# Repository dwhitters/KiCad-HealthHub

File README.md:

# KiCad-HealthHub
Schematic and PCB layout for the health hub.

## Overview
This PCB provides basic signal processing for an ECG input. The processed signal is then fed into a bluetooth module that can be used to provide data to a corresponding phone app, such as https://github.com/DaveAldon/Health-Hub-Mobile. Additional microcontroller pins are broken out to facilitate development of additional features.

## Images
Front

Back

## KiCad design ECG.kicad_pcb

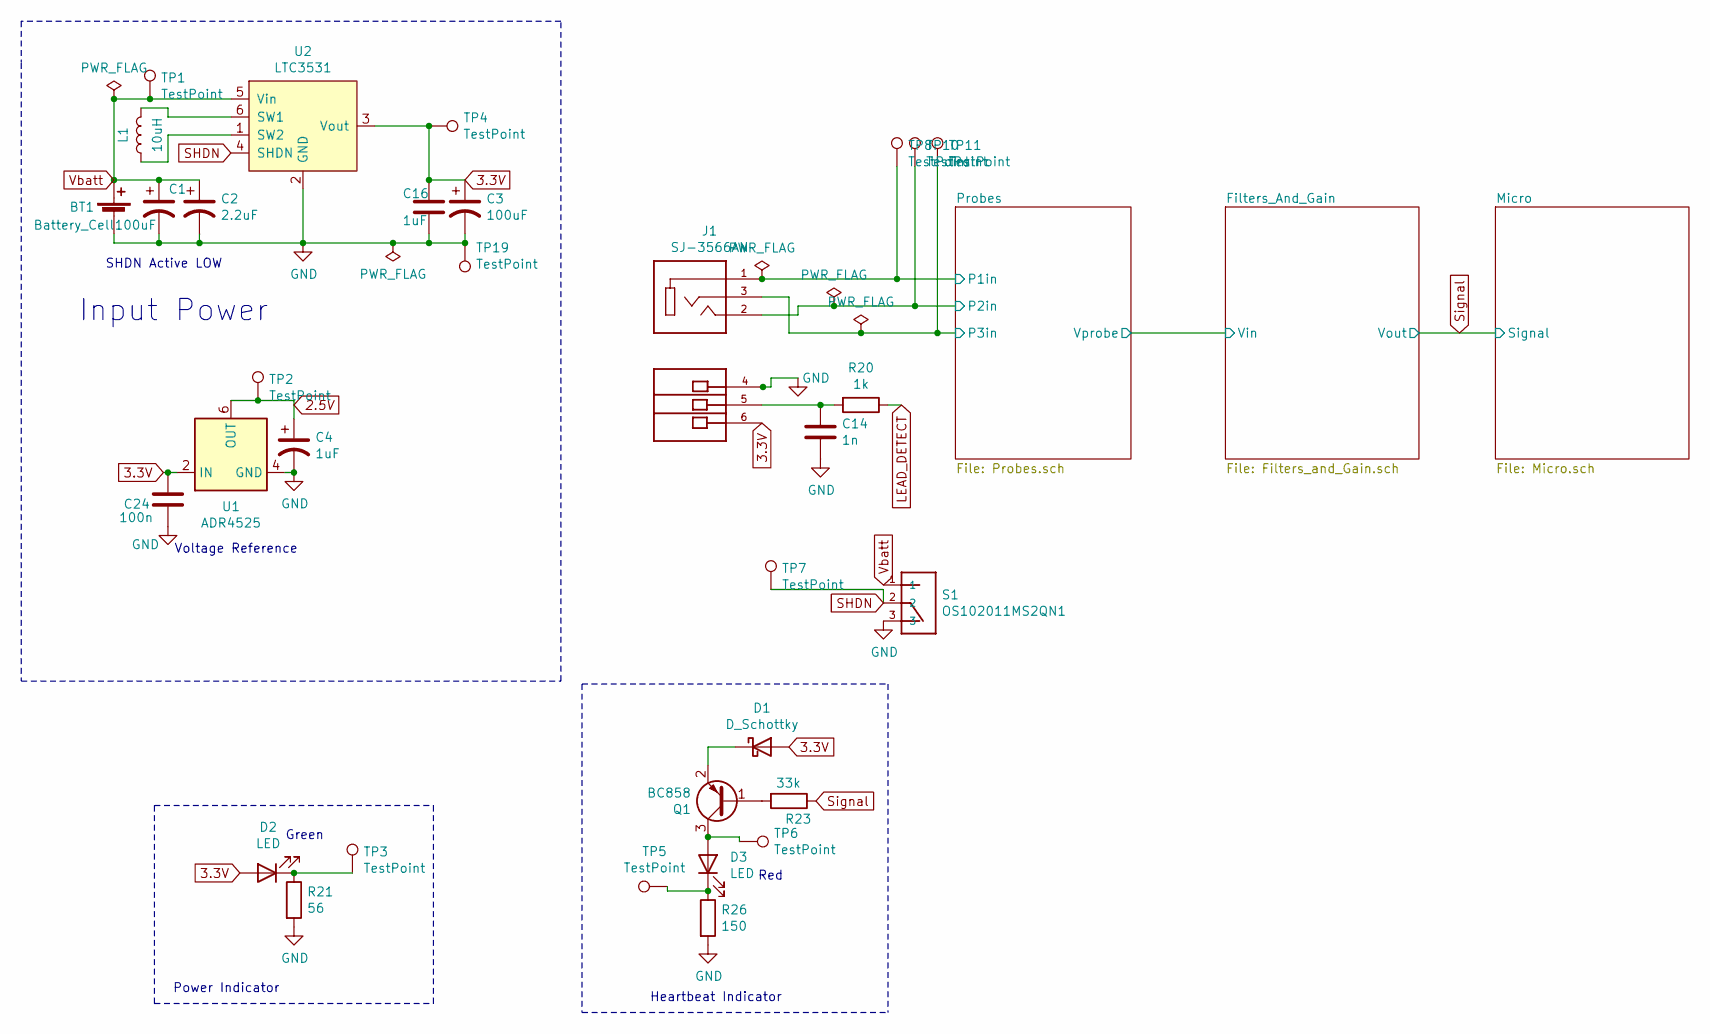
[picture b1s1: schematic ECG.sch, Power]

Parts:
BT1: Battery_Cell; BatteryHolder_Keystone_3008_1x2450
C1, C3: 100uF; CP_Elec_6.3x5.3
C2: 2.2uF; CP_Elec_4x5.7
C4: 1uF; C_0805_2012Metric_Pad1.18x1.45mm_HandSolder
C14: 1n; C_0805_2012Metric_Pad1.18x1.45mm_HandSolder
C16: 1uF; CP_Elec_4x5.3
C24: 100n; C_0805_2012Metric_Pad1.18x1.45mm_HandSolder
D1: D_Schottky; D_0603_1608Metric_Pad1.05x0.95mm_HandSolder
D2, D3: LED; D_0603_1608Metric_Pad1.05x0.95mm_HandSolder
J1: SJ-3566AN; CUI_SJ-3566AN
L1: 10uH; L_Sumida_CDRH5D28
Q1: BC858; SOT-23
R20: 1k; R_0805_2012Metric_Pad1.20x1.40mm_HandSolder
R21: 56; R_0805_2012Metric_Pad1.20x1.40mm_HandSolder
R23: 33k; R_0805_2012Metric_Pad1.20x1.40mm_HandSolder
R26: 150; R_0805_2012Metric_Pad1.20x1.40mm_HandSolder
S1: OS102011MS2QN1; SW_OS102011MS2QN1
TP1, TP3, TP5, TP6, TP7, TP8, TP10, TP11: TestPoint; TestPoint_Pad_D2.0mm
TP2, TP4, TP19: TestPoint; TestPoint_Pad_D4.0mm
U1: ADR4525; SOIC-8_3.9x4.9mm_P1.27mm
U2: LTC3531; TSOT-23-6

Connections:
2.5V: C4.1, TP2.1, U1.6 (OUT); also elsewhere on the board
3.3V: C3.1, C16.1, C24.1, D1.2 (A), D2.2 (A), J1.6, TP4.1, U1.2 (IN), U2.3 (Vout); also elsewhere on the board
/Probes/P1in: J1.1, TP8.1; also elsewhere on the board
/Probes/P2in: J1.2, TP10.1; also elsewhere on the board
/Probes/P3in: J1.3, TP11.1; also elsewhere on the board
GND: BT1.2 (-), C1.2, C2.2, C3.2, C4.2, C14.2, C16.2, C24.2, J1.4, R21.2, R26.2, S1.3, TP19.1, U1.4 (GND), U2.2 (GND); also elsewhere on the board
LEAD_DETECT: R20.1; also elsewhere on the board
unnamed: C14.1, J1.5, R20.2
unnamed: D1.1 (K), Q1.2 (E)
unnamed: D2.1 (K), R21.1, TP3.1
unnamed: D3.1 (K), R26.1, TP5.1
unnamed: D3.2 (A), Q1.3 (C), TP6.1
unnamed: L1.1, U2.1 (SW2)
unnamed: L1.2, U2.6 (SW1)
unnamed: Q1.1 (B), R23.2
SHDN: S1.2, TP7.1, U2.4 (SHDN); also elsewhere on the board
Signal: R23.1; also elsewhere on the board
Vbatt: BT1.1 (+), C1.1, C2.1, S1.1, TP1.1, U2.5 (Vin); also elsewhere on the board

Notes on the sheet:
Input Power
Voltage Reference
SHDN Active LOW
Power Indicator
Green
Red
Heartbeat Indicator

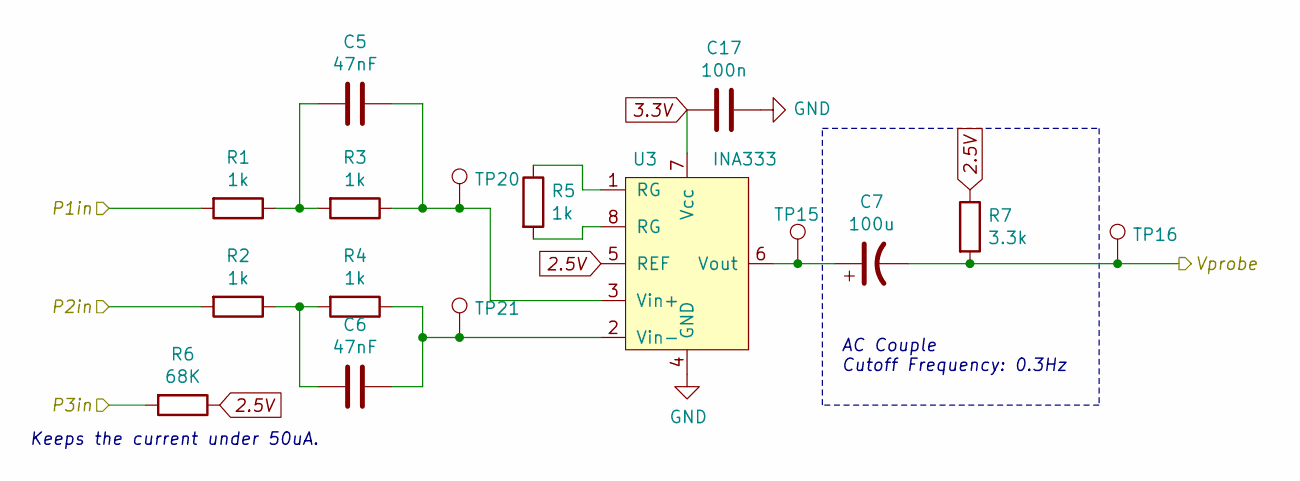
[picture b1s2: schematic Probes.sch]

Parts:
C5, C6: 47nF; C_0805_2012Metric_Pad1.18x1.45mm_HandSolder
C7: 100u; C_1210_3225Metric_Pad1.33x2.70mm_HandSolder
C17: 100n; C_0805_2012Metric_Pad1.18x1.45mm_HandSolder
R1, R2, R3, R4, R5: 1k; R_0805_2012Metric_Pad1.20x1.40mm_HandSolder
R6: 68K; R_0805_2012Metric_Pad1.20x1.40mm_HandSolder
R7: 3.3k; R_0805_2012Metric_Pad1.20x1.40mm_HandSolder
TP15, TP16, TP20, TP21: TestPoint; TestPoint_Pad_D2.0mm
U3: INA333; VSSOP-8_3.0x3.0mm_P0.65mm

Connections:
2.5V: R6.1, R7.1, U3.5 (REF); also elsewhere on the board
3.3V: C17.2, U3.7 (Vcc); also elsewhere on the board
/Filters_And_Gain/Vin: C7.2, R7.2, TP16.1; also elsewhere on the board
/Probes/P1in: R1.2; also elsewhere on the board
/Probes/P2in: R2.2; also elsewhere on the board
/Probes/P3in: R6.2; also elsewhere on the board
GND: C17.1, U3.4 (GND); also elsewhere on the board
unnamed: C5.1, R3.1, TP20.1, U3.3 (Vin+)
unnamed: C5.2, R1.1, R3.2
unnamed: C6.1, R4.1, TP21.1, U3.2 (Vin-)
unnamed: C6.2, R2.1, R4.2
unnamed: C7.1, TP15.1, U3.6 (Vout)
unnamed: R5.1, U3.1 (RG)
unnamed: R5.2, U3.8 (RG)

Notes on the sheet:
Keeps the current under 50uA.
AC Couple Cutoff Frequency: 0.3Hz

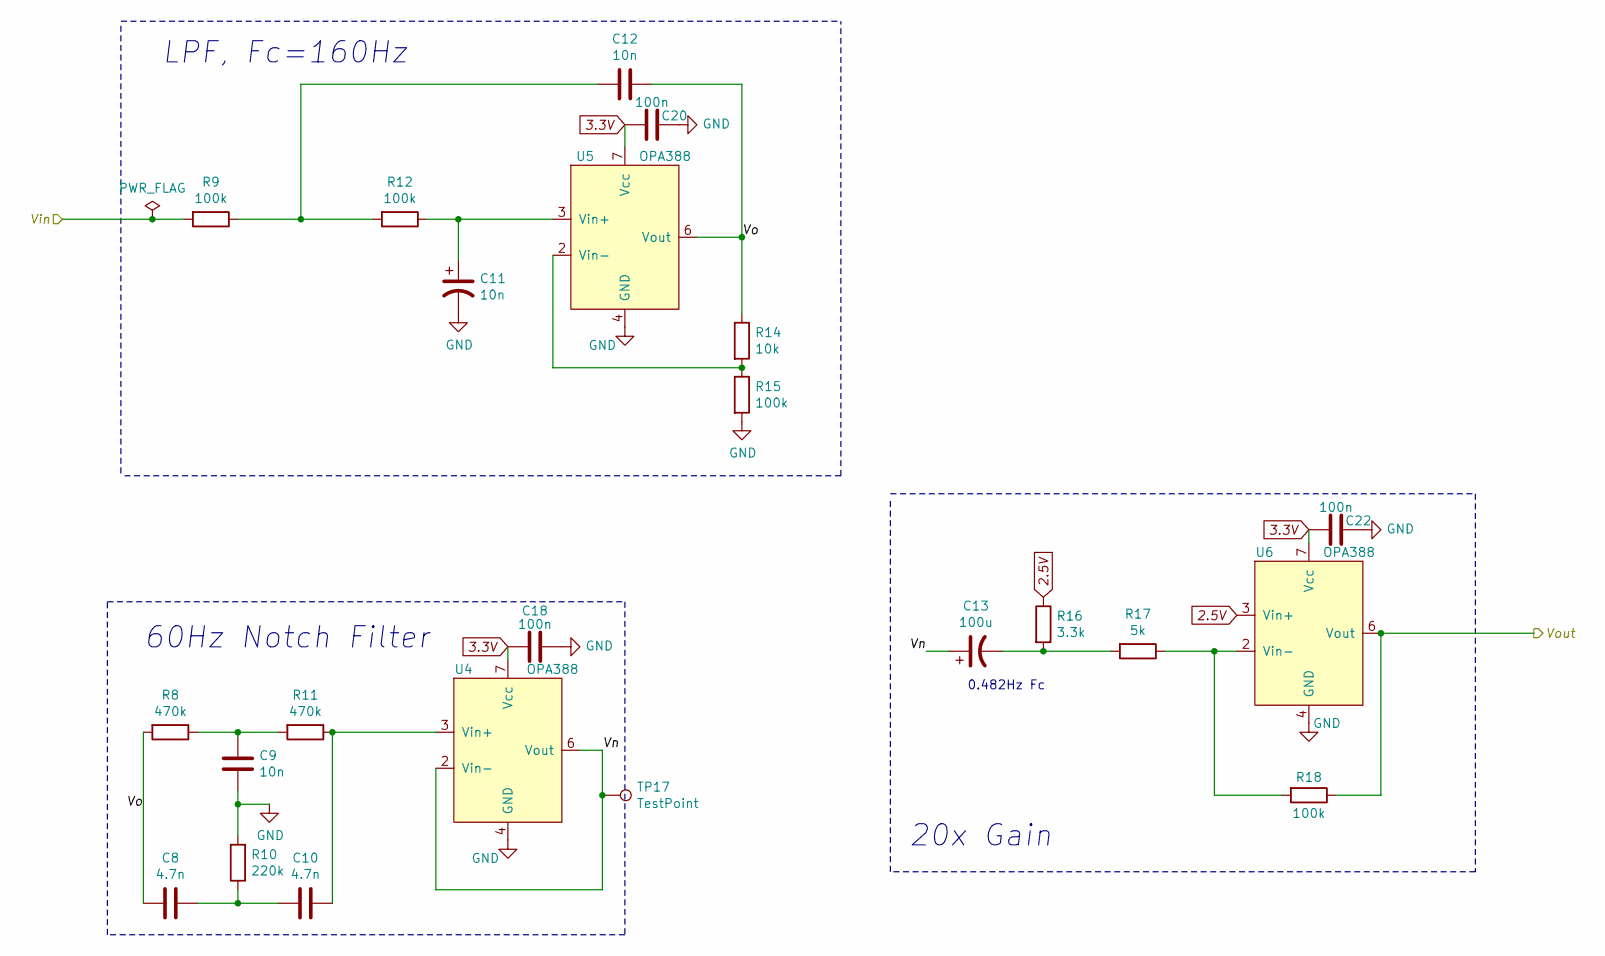
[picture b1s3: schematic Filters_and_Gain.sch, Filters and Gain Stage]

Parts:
C8, C10: 4.7n; C_0805_2012Metric_Pad1.18x1.45mm_HandSolder
C9, C11, C12: 10n; C_0805_2012Metric_Pad1.18x1.45mm_HandSolder
C13: 100u; C_1210_3225Metric_Pad1.33x2.70mm_HandSolder
C18, C20, C22: 100n; C_0805_2012Metric_Pad1.18x1.45mm_HandSolder
R8, R11: 470k; R_0805_2012Metric_Pad1.20x1.40mm_HandSolder
R9, R12, R15, R18: 100k; R_0805_2012Metric_Pad1.20x1.40mm_HandSolder
R10: 220k; R_0805_2012Metric_Pad1.20x1.40mm_HandSolder
R14: 10k; R_0805_2012Metric_Pad1.20x1.40mm_HandSolder
R16: 3.3k; R_0805_2012Metric_Pad1.20x1.40mm_HandSolder
R17: 5k; R_0805_2012Metric_Pad1.20x1.40mm_HandSolder
TP17: TestPoint; TestPoint_Pad_D2.0mm
U4, U5, U6: OPA388; SOIC-8_3.9x4.9mm_P1.27mm

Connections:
2.5V: R16.1, U6.3 (Vin+); also elsewhere on the board
3.3V: C18.1, C20.1, C22.1, U4.7 (Vcc), U5.7 (Vcc), U6.7 (Vcc); also elsewhere on the board
/Filters_And_Gain/Vin: R9.2; also elsewhere on the board
/Filters_And_Gain/Vn: C13.1, TP17.1, U4.2 (Vin-), U4.6 (Vout)
/Filters_And_Gain/Vo: C8.2, C12.2, R8.2, R14.1, U5.6 (Vout)
GND: C9.1, C11.2, C18.2, C20.2, C22.2, R10.2, R15.2, U4.4 (GND), U5.4 (GND), U6.4 (GND); also elsewhere on the board
unnamed: C9.2, R8.1, R11.2
unnamed: C10.1, R11.1, U4.3 (Vin+)
unnamed: C8.1, C10.2, R10.1
unnamed: C11.1, R12.1, U5.3 (Vin+)
unnamed: C12.1, R9.1, R12.2
unnamed: C13.2, R16.2, R17.2
unnamed: R14.2, R15.1, U5.2 (Vin-)
unnamed: R17.1, R18.2, U6.2 (Vin-)
Signal: R18.1, U6.6 (Vout); also elsewhere on the board

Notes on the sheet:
LPF, Fc=160Hz
20x Gain
0.482Hz Fc
60Hz Notch Filter

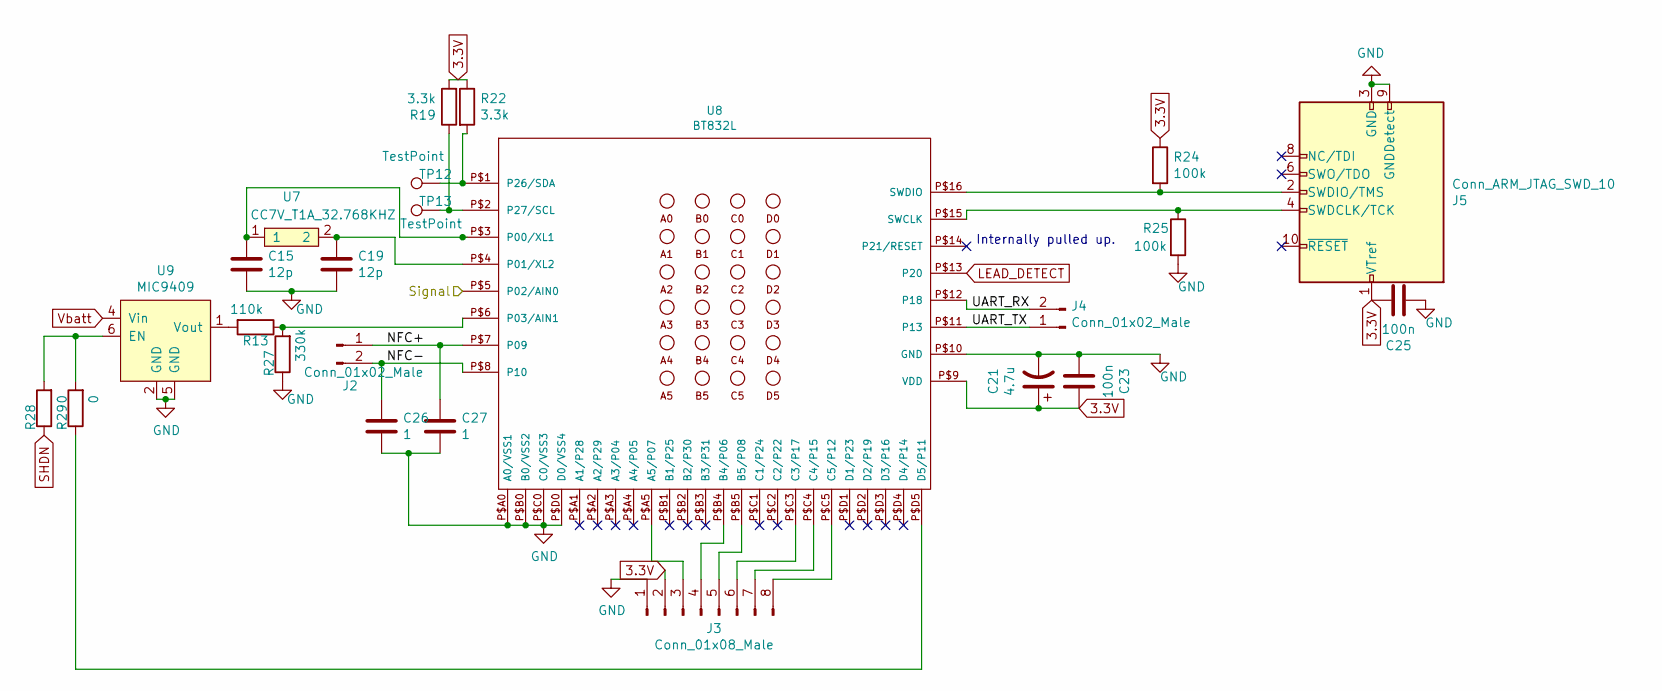
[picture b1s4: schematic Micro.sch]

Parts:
C15, C19: 12p; C_0805_2012Metric_Pad1.18x1.45mm_HandSolder
C21: 4.7u; CP_Elec_4x5.3
C23, C25: 100n; C_0805_2012Metric_Pad1.18x1.45mm_HandSolder
C26, C27: 1; C_0805_2012Metric_Pad1.18x1.45mm_HandSolder
J2, J4: Conn_01x02_Male; PinHeader_1x02_P2.00mm_Vertical
J3: Conn_01x08_Male; PinHeader_1x08_P2.00mm_Vertical
J5: Conn_ARM_JTAG_SWD_10; PinHeader_2x05_P1.27mm_Vertical_SMD
R13: 110k; R_0805_2012Metric_Pad1.20x1.40mm_HandSolder
R19, R22: 3.3k; R_0805_2012Metric_Pad1.20x1.40mm_HandSolder
R24, R25: 100k; R_0805_2012Metric_Pad1.20x1.40mm_HandSolder
R27: 330k; R_0805_2012Metric_Pad1.20x1.40mm_HandSolder
R28, R29: 0; R_0402_1005Metric_Pad0.72x0.64mm_HandSolder
TP12, TP13: TestPoint; TestPoint_Pad_D2.0mm
U7: CC7V_T1A_32.768KHZ; CC7V_T1A
U8: BT832L; BT832-BT832L
U9: MIC9409; SOT-363_SC-70-6_Handsoldering

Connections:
3.3V: C21.1, C23.1, C25.1, J3.2, J5.1 (VTref), R19.2, R22.1, R24.1, U8.P$9 (VDD); also elsewhere on the board
/Micro/NFC+: C27.1, J2.1, U8.P$7 (P09)
/Micro/NFC-: C26.1, J2.2, U8.P$8 (P10)
/Micro/UART_RX: J4.2, U8.P$12 (P18)
/Micro/UART_TX: J4.1, U8.P$11 (P13)
GND: C15.2, C19.2, C21.2, C23.2, C25.2, C26.2, C27.2, J3.1, J5.3 (GND), J5.5 (GND), J5.9 (GNDDetect), R25.2, R27.1, U8.P$10 (GND), U8.P$A0 (A0/VSS1), U8.P$B0 (B0/VSS2), U8.P$C0 (C0/VSS3), U8.P$D0 (D0/VSS4), U9.2 (GND), U9.5 (GND); also elsewhere on the board
LEAD_DETECT: U8.P$13 (P20); also elsewhere on the board
unnamed: C15.1, U7.1, U8.P$3 (P00/XL1)
unnamed: C19.1, U7.2, U8.P$4 (P01/XL2)
unnamed: J3.3, U8.P$A5 (A5/P07)
unnamed: J3.4, U8.P$B4 (B4/P06)
unnamed: J3.5, U8.P$B5 (B5/P08)
unnamed: J3.6, U8.P$C3 (C3/P17)
unnamed: J3.7, U8.P$C4 (C4/P15)
unnamed: J3.8, U8.P$C5 (C5/P12)
unnamed: J5.2 (SWDIO/TMS), R24.2, U8.P$16 (SWDIO)
unnamed: J5.4 (SWDCLK/TCK), R25.1, U8.P$15 (SWCLK)
unnamed: R13.1, R27.2, U8.P$6 (P03/AIN1)
unnamed: R13.2, U9.1 (Vout)
unnamed: R19.1, TP13.1, U8.P$2 (P27/SCL)
unnamed: R22.2, TP12.1, U8.P$1 (P26/SDA)
unnamed: R28.2, R29.2, U9.6 (EN)
unnamed: R29.1, U8.P$D5 (D5/P11)
SHDN: R28.1; also elsewhere on the board
Signal: U8.P$5 (P02/AIN0); also elsewhere on the board
Vbatt: U9.4 (Vin); also elsewhere on the board

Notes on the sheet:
Internally pulled up.

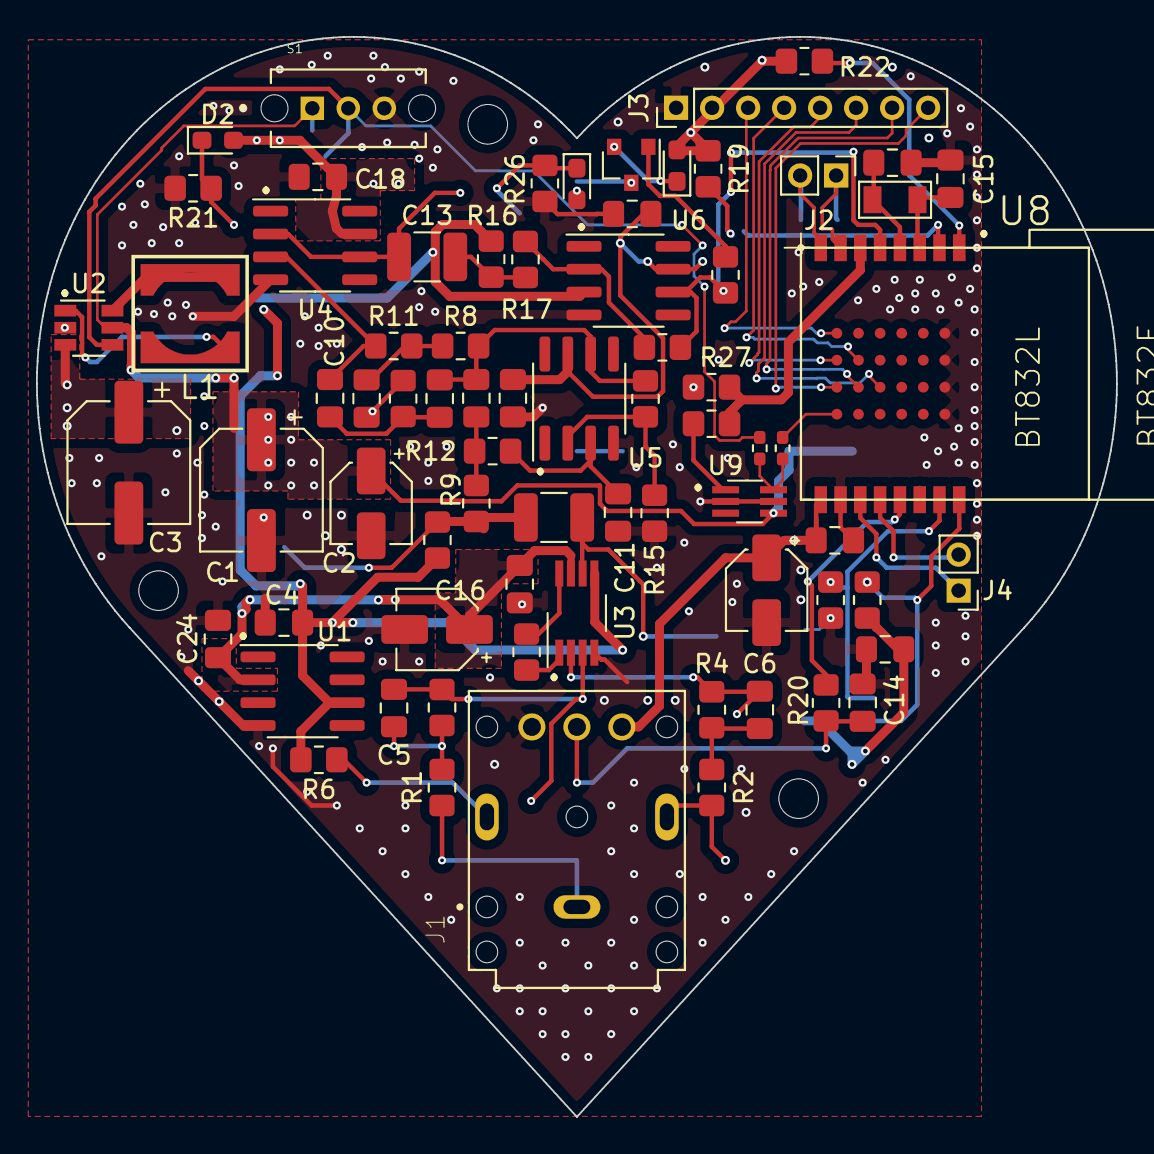
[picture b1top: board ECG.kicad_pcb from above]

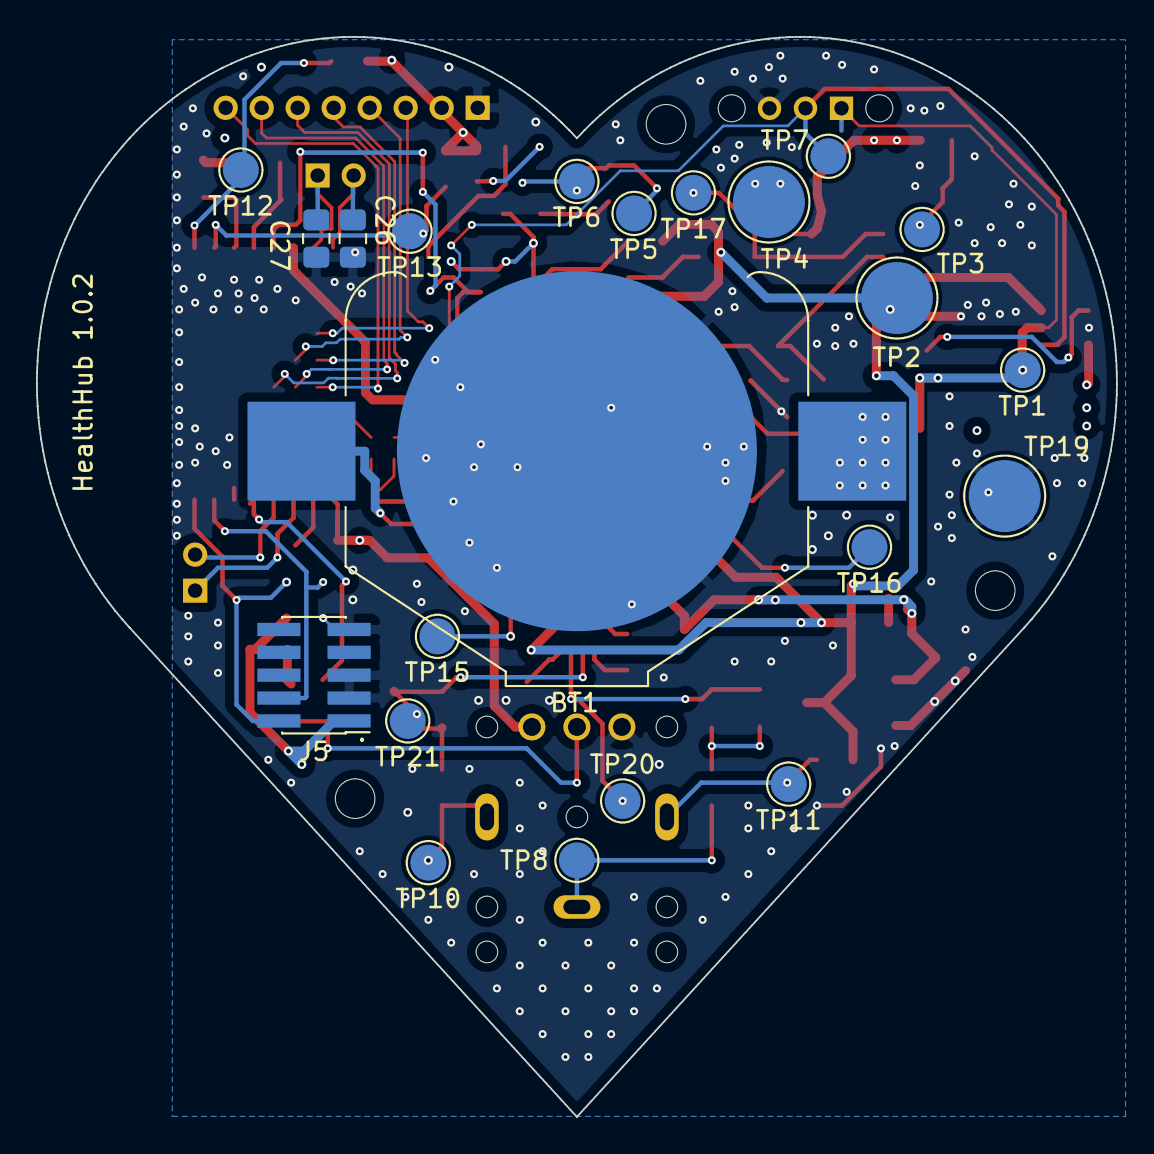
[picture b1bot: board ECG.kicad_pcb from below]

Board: 4 copper layers, 60.0 x 60.0 mm, 95 parts (22 on the bottom side), 56 nets.

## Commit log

2020-10-27 Initial commit. Added voltage regulator and reference.
2020-10-28 Completed power circuits
2020-10-28 First pass at schematic complete
2020-10-28 Added datasheet link to OPA388 component
2020-11-12 Assigned footprints
2020-11-12 Added components to pcb
2020-11-16 Added battery circuit
2020-11-18 #1 - Create PCB footprints
2020-11-23 #2 - Add ECG input via headphone jack
2020-11-24 #3 - Add power switch
2020-11-25 #7 - Add ADC
2020-12-02 #9 - Add heartbeat indicator
2020-12-02 #8 - Add test points. (Also updated filter circuit)
2020-12-03 #4 - Added the heart edge cut and updated the Kicad footprints that were removed
2020-12-04 Added bypass caps on ICs and fixed the SHDN input.
2020-12-04 Added bypass cap to Vref input
2020-12-05 Removed extra caps and removed the tantalum cap as it was too large
2020-12-05 Added battery voltage monitoring
2020-12-07 Added GND to I2C header and added ground and power planes.
2020-12-08 #4 - Initial component placement complete. Increased board size.
2020-12-08 #4 - Cleaned up ERC errors and updated the I2C pinout to increase board NET clearance
2020-12-10 #10 - Create BT symbol
2020-12-12 #11 - Create BT Footprint
2020-12-13 #5 - Added 3.3V buck-boost regulator
2020-12-16 #13 and #5 - Updated circuits for 3.3V power rail
2020-12-17 #6 - Add bluetooth module to board.
2020-12-21 #6 #14 - Add bluetooth and flash header to board
2020-12-21 #16 - Used Fanstel library
2020-12-26 #4 - Placed new components
2020-12-29 Initial routing
2020-12-30 #4 - Routed board
2021-01-03 Added NFC tuning cap footprints, cleaned up silkscreen, and connected planes
2021-01-03 Added images
2021-01-03 Added name and version to silkscreen
2021-01-03 Added pin 1 designators
2021-01-03 Fixed power and ground pours
2021-01-04 Updated ground pour and fixed C23 silkscreen
2021-01-04 Updated front image
2021-02-04 #21 - Hook up switch to battery line
2021-02-04 #19 and #20 - Fix the micro debug and power connections
2021-02-04 #22 - Detach battery ADC while the micro is not powered
2021-02-04 Updated silk screen
2021-02-11 #24 - Updated AC couple
2021-02-22 #23 - Add high side power switcher
2021-02-23 Removed test point tags
2021-03-01 #24 - Flip PNP and update low pass filter output resistors
2021-03-01 #24 - Update layout with flipped PNP and update images
2021-03-29 Added mounting holes, Added lead-detect to a micro GPIO, and removed requirement that the leads must be attached prior to turning on the device
2021-03-29 Updated revision on PCB
2021-03-29 Connected high side power switcher enable pin to SHDN net instead of 3.3V. Prevents feedback on the 3.3V net from registering as a logic high and keeping the power going through
2021-04-01 #25 - Updated low pass filter. Gain 2x -> 1x. Added ADC divider for battery to account for brand new batteries.
2021-04-02 #28 - Remove pulldown from reset line on micro
2021-04-02 Updated debug header to include 3.3V and GND
2021-04-08 #27 - Fix gain stage clipping
2021-04-08 Prettified the board and removed old gerbers
2021-04-08 Removed old zip file
2021-04-20 Moved silkscreen references on PCB
